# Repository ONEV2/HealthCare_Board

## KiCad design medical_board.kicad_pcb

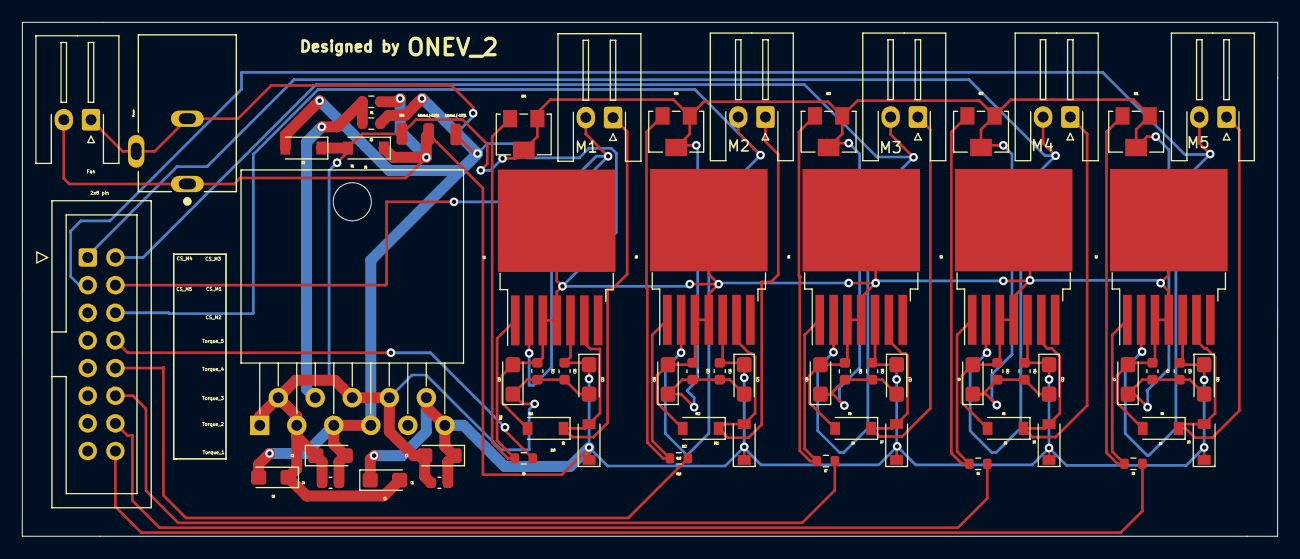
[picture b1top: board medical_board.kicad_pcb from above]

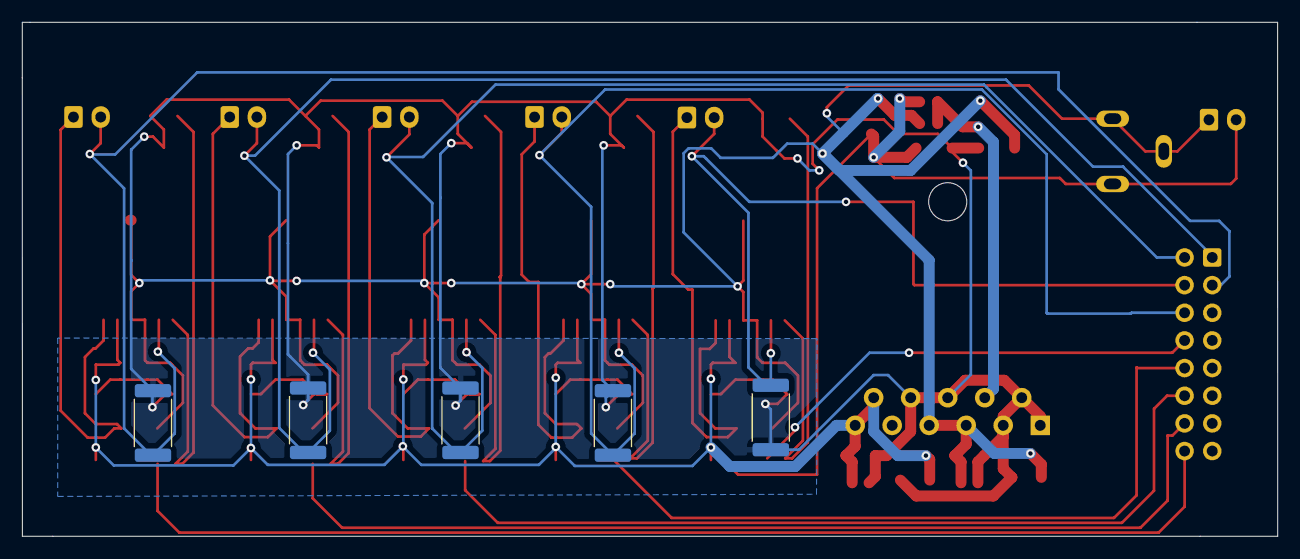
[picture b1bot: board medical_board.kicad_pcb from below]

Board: 2 copper layers, 115.3 x 47.2 mm, 72 parts (5 on the bottom side), 24 nets.

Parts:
2x8 pin: IDC-Header_2x08_P2.54mm_Vertical
C1, C4, C9, C10, C13, C14, C16, C18, C21, C22, C25, C26: 0.1uF; C_0603_1608Metric
C2, C3, C5, C6, C7, C8, C11, C12, C15, C17, C19, C20, C23, C24: 10uF; CP_EIA-3216-18_Kemet-A
D1, D2: D_Zener; D_SOD-123
D3, D4, D5, D6, D7, D8, D9, D10, D11, D12: D_Schottky; D_SOD-123
External_(+12V)1: Conn_01x01; SolderWirePad_1x01_SMD_1x2mm
External_(-12V)1: Conn_01x01; SolderWirePad_1x01_SMD_1x2mm
Fan: JST_XH_S2B-XH-A-1_1x02_P2.50mm_Horizontal
GND: Conn_01x01; SolderWirePad_1x01_SMD_1x2mm
M1, M2, M3, M4, M5: JST_XH_S2B-XH-A-1_1x02_P2.50mm_Horizontal
Power: CUI_PJ-102A
R1, R2: 100k; R_0603_1608Metric
R3, R4, R7, R9, R10: 49k; R_0603_1608Metric
R5, R6, R8, R11, R12: 0.1; R_2512_6332Metric
RV1, RV2, RV3, RV4, RV5: 1k; Potentiometer_Bourns_3224W_Vertical
U1: OPAMP; TO-220-11_P3.4x2.54mm_StaggerOdd_Lead5.84mm_TabDown
U2, U3, U4, U5, U6: OPAMP; TO-263-7_TabPin8

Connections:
+V: C1.1, C3.1, C5.1, C11.1, C12.1, C13.1, C14.1, C17.1, C18.1, C23.1, C24.1, C25.1, C26.1, D1.1 (K), D3.1 (K), D5.1 (K), D7.1 (K), D9.1 (K), D11.1 (K), External_(+12V)1.1, Fan.2, Power.1, R1.1, U1.10, U1.11, U2.5 (V-), U3.5 (V-), U4.5 (V-), U5.5 (V-), U6.5 (V-)
-V: C2.2, C4.1, C6.2, C7.2, C8.2, C9.1, C10.1, C15.2, C16.1, C19.2, C20.2, C21.1, C22.1, D2.2 (A), D4.2 (A), D6.2 (A), D8.2 (A), D10.2 (A), D12.2 (A), External_(-12V)1.1, Fan.1, Power.2, Power.3, R2.2, U1.5 (V-), U1.7, U2.3, U2.4 (V+), U2.8, U3.3, U3.4 (V+), U3.8, U4.3, U4.4 (V+), U4.8, U5.3, U5.4 (V+), U5.8, U6.3, U6.4 (V+), U6.8
GND: C1.2, C2.1, C3.2, C4.2, C5.2, C6.1, C7.1, C8.1, C9.2, C10.2, C11.2, C12.2, C13.2, C14.2, C15.1, C16.2, C17.2, C18.2, C19.1, C20.1, C21.2, C22.2, C23.2, C24.2, C25.2, C26.2, D1.2 (A), D2.1 (K), GND.1, R5.2, R6.2, R8.2, R11.2, R12.2, RV1.1, RV1.2, RV2.1, RV2.2, RV3.1, RV3.2, RV4.1, RV4.2, RV5.1, RV5.2, U1.1 (+), U1.2 (-), U1.3, U1.6, U1.8
unnamed: D3.2 (A), D4.1 (K), M5.1, U2.6
unnamed: D5.2 (A), D6.1 (K), M4.1, U3.6
unnamed: D7.2 (A), D8.1 (K), M3.1, U4.6
unnamed: D9.2 (A), D10.1 (K), M1.1, U5.6
unnamed: D11.2 (A), D12.1 (K), M2.1, U6.6
unnamed: 2x8 pin.3, M5.2, R5.1, U2.2 (-)
unnamed: 2x8 pin.1, M4.2, R6.1, U3.2 (-)
unnamed: 2x8 pin.2, M3.2, R8.1, U4.2 (-)
unnamed: 2x8 pin.4, M1.2, R11.1, U5.2 (-)
unnamed: 2x8 pin.6, M2.2, R12.1, U6.2 (-)
unnamed: R1.2, R2.1, U1.4 (V+)
unnamed: R3.2, RV1.3, U2.1 (+)
unnamed: R4.2, RV2.3, U3.1 (+)
unnamed: R7.2, RV3.3, U4.1 (+)
unnamed: R9.2, RV4.3, U5.1 (+)
unnamed: R10.2, RV5.3, U6.1 (+)
T1: 2x8 pin.8, R9.1
T2: 2x8 pin.10, R10.1
T3: 2x8 pin.12, R7.1
T4: 2x8 pin.14, R4.1
T5: 2x8 pin.16, R3.1

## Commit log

2022-08-03 Add:Kicad files
2022-08-03 Updated Routing files
